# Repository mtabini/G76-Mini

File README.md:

# G76 Mini - A $10 VGA interface for homebrew retrocomputing

The G76 Mini is a simple and inexpensive VGA module for homebrew retrocomputing projects. It requires only a handful of easy-to-procure components and can be either integrated into SBC designs or as a standalone board that can interface with most 8-bit architectures (though it was built with the 6502 in mind). You can view a demo of the interface running [on YouTube](https://youtu.be/on7V5krxY_A).

The hardware design uses the EPM240 from the [Max II family](https://www.intel.com/content/dam/altera-www/global/zh_CN/pdfs/literature/hb/max2/max2_mii5v1_01.pdf) by Altera (now Intel), but the SystemVerilog code should be easily portable to other CPLDs or FPGAs, since it doesn't use any proprietary IP. The EPM240, while technically obsolete, can easily be obtained for around $3 (as of May 2022) on eBay or AliExpress; with the added cost of SRAM and passives, the interface can be incorporated into an existing design for around $5, or built as a standalone board for around $10.

It is additionally possible to completely avoid having to solder SMD parts by purchasing a MAX II EPM240 minimal development board and building a shield on top of it. These typically cost $10 on sites like AliExpress and come with a USB Blaster JTAG programmer to boot.

## Features

The G76 Mini supports these features:

- Completely asynchronous operation; you should be able to just bitbang data into the registers at the typical speeds supported by most hobbyist retrocomputing projects.
- 320x240 resolution at 8BPP (RRRGGGBB), rendered as a 640x480 @ 60Hz standard VGA signal.
- 640x240 resolution at 4BPP “high res” mode using a CGA-like palette, capable of 80x30 text (though you will have to implement the text rendering in software).
- Full read and write access to the video RAM through a set of interface registers.
- Hardware-accelerated vertical scrolling (handy for text displays).
- Toggable self-incrementing X coordinate for faster data transfers.
- Active-low interrupt when entering the non-visible area at the bottom of the screen.

### Features that almost made the cut

The design doesn't support tiling or sprites; there just isn't enough space for them in the EPM240. This is something that I eventually plan to add (possibly after some additional cleanup), but it will likely require more expensive—or, at least, more powerful—hardware.

It should be possible to rewrite the video rendering code to use the 640x400 @ 72Hz VGA mode, thus supporting 8PP even in high-res mode. I am not sure, however, that the design would still fit in an EPM240, and every monitor in my possession struggles to support that resolution, so I didn't really bother with it. An interesting alternative would be to still use 640x480 @ 60Hz, but only render 400 vertical lines through the judicious use of borders.

Finally, there currently is no reset mechanism. Though initially an oversight, this eventually proved to be a requirement to fit the design within the available number of gates.

## Programming guide

The G76 Mini implements 6 addressable 8-bit registers:

| Address | Description |
| --- | --- |
| 0 | Low 8-bits of X coordinate |
| 1 | Bit 0: High bit of X coordinate<br>Bits 1-7: Unused |
| 2 | Y coordinate |
| 3 | Pixel Data |
| 4 | Control<br>Bit 0: Enable/disable X coordinate auto-increment<br>Bit 1: Enable/disable high res mode<br>Bit 2: Enable/disable vertical blank interrupt signal<br>Bit 3: Vertical blank status (read-only)<br>Bits 4-7: Unused<br><br>Writing to this register also clears the vertical blanking interrupt.|
| 5 | Y Offset |

In order to write a single pixel, you first set the X and Y coordinates (in any order), then write the appropriate color value in the Pixel Data register. The new value is placed in the interface's internal memory approximately 60ns later, at which point the system is ready for a new pixel (note, however, that you can start setting new coordinates after only approximately 20ns). Unless auto-increment mode is on, the X and Y coordinates are preserved indefinitely; this helps minimize the need to write data to the coordinate registers, thus speeding up operations.

Reading works in the same way, including support for automatic X-coordinate increment.

### Using auto-increment mode

If Bit 0 of the Control register is set, the internal address pointer is incremented by 1 every time a new value is written to or read from the Pixel Data register. This allows you to read and write entire rows of pixels without having to reset the coordinates every time. 

Note that the increment mechanism is unaware of the system's internal memory layout; thus, if you are in high-res mode, the X coordinate is incremented by _two_ pixels with every access, and, if you exceed the horizontal resolution, you will have to access another 80 values to the Pixel Data register before ending up at the beginning of the next visible line (in practice, you will simply want to reset your coordinates to the beginning of the next line).

### Using hardware-accelerated Y scrolling

Writing a value into the Y Offset register causes the display to be shifted down (that is, scroll up) by a corresponding number of lines. This feature is designed to aid in the implementation of text displays, since the G76 Mini doesn't support any text modes and re-rendering the entire screen would be exceedingly slow. Instead, when the cursor reaches the end of the screen, a new line of text can be rendered beyond the bottom of the display (i.e.: starting at row 240), and then the Y Offset register incremented by the pixel height of the font used.

Note that the Y coordinate register is _relative_ to the Y offset. That means that “Y coordinate 0” is always the top row of the _visible_ portion of the display, regardless of what the Y Offset register is set to.

### Using high-res mode

When bit 1 of the Control register is set, the interface switches to “high res” mode, which displays 640x240 pixels at 4BPP; if you use an 8x8 pixel font, this allows you to display text at 80 columns by 30 rows.

In this mode, each nibble describes a pixel, which is rendered using a palette that approximates the original 16-color CGA mode:

| Value | Color |
| --- | --- |
| 0 | Black |
| 1 | Blue |
| 2 | Green |
| 3 | Cyan | 
| 4 | Red |
| 5 | Magenta |
| 6 | Brown |
| 7 | Grey |
| 8 | Dark grey |
| 9 | Light blue |
| 10 | Light green |
| 11 | Light cyan |
| 12 | Light red |
| 13 | Light magenta |
| 14 | Yellow |
| 15 | White |

Note that the X coordinate register is unaware of the difference in resolution between standard and high-res modes; therefore, you can only really address two pixels at a time, and will always end up accessing an even coordinate by default (e.g.: writing a byte to “x coordinate 0” writes both pixels at `x=0` and `x=1`). This is caused by the fact that, internally, reading a byte value so that individual bits could be updated would be too time-intensive, and so I left it purposefully out of the design. It makes high-res mode much less useful for dynamic display, though it is, of course, still possible to do so.

## Synchronizing with the screen's vertical refresh

If you enable bit 2 of the Control Register, the system brings the  `/VOUT_IRQ` line low when the screen rendering enters the vertical blanking interval, thus allowing you to synchronize your screen updates to the monitor's natural refresh rate for flicker-free animations.

Note that the line remains asserted low until you write any value to the Control register (you can simply read the register and write back onto itself so that you won't make any changes to it), or until you disable interrupts altogether. This is important: If you don't clear the interrupt before exiting your interrupt handler, your computer will likely get stuck in a perpetual loop!

When writing software for a computer that uses the G76 Mini, you should plan for the fact that the interface could be pulling the IRQ line low on soft boot, and therefore should clear it explicitly on boot before you allow the CPU to process interrupts.

If you don't want to deal with interrupts at all, you can simply synchronously observe bit 3 of the Control register, which the interface sets to 1 whenever the raster is in the blanking interval.

## Hardware interface

The hardware interface requires 8 data lines and 3 address lines to access the registers, as well as a Chip Select (active high), and a Read/Write (active low) line. Data is written on the rising edge of Read/Write when Chip Select is high. Data and address lines need to be valid for approximately 20ns after Read/Write rises to allow the CPLD to read the values.

Optionally, a `/VOUT_IRQ` line, active low, can be used to detect when the display raster enters the non-visible zone at the end of the screen; this enables synchronized rendering to avoid flickering.

The interface operates at 3.3V and is **not 5V safe.** Interoperation with a 5V design should be possible using a level shifter, but this is as yet untested.

## Interfacing considerations

The G76 Mini reads data when the `MPU_CS` signal goes high (and, for write operations, when the `/MPU_WE` signal goes low). This makes it compatible with most 8-bit CPUs like the Z80 and 6502, so long as you provide the glue logic required to control the `MPU_CS` signal.

In a design based on the 6502, this means that you will need to qualify `MPU_CS` with the CPU's clock signal, because the CPU doesn't place a valid address on the bus until the high part of the clock cycle. Thus, `MPU_CS` can only go high at the same time as the `PHI2` signal that provides the clock.

## Reference design

I have included a [simple reference design](/reference_design/schematic.pdf) ([B/W version](/reference_design/schematic_bw.pdf)) for a standalone video card in the project. As you can see from the schematic, the interface really only needs a handful of components and is quite simple, since it depends so heavily on the CPLD.

The VGA output is generated using a few resistors, and is of surprisingly good quality, especially if you stick with 1% tolerances. An R2R network might produce a more consistent result, and of course a DAC would be best, but it seemed overkill for a homebrew project.

I picked the [CY7C1018DV33-10VXI](https://www.mouser.ca/datasheet/2/100/CYPR_S_A0001416448_1-2540640.pdf), an inexpensive (about $3.50 from any major North American distributor as of April 2022) 128kiB, 10ns SRAM chip from Cypress as the video memory for the reference design. I suspect that any 3.3V-compatible chip with cycle times of 20ns or faster would work equally well, though I have not tested with anything else.

### Programming the CPLD

The Max II can be programmed using Altera's [USB Blaster](https://www.intel.com/content/www/us/en/products/sku/215633/intel-fpga-download-cable/specifications.html), which has been imaginatively renamed the “FPGA Download Cable” by Intel. (Perhaps they should change their name to “Chip Manufacturing Corporation”.) Clones of the USB Blaster are readily available on Amazon, eBay, and AliExpress for just a few dollars—in fact, most sellers bundle it with their Max II development boards, which are sometimes cheaper than the JTAG programmer alone.

The G76 Mini's SystemVerilog source can be compiled using Quartus II; you should be able to just open the [VGA320.qpf](./VGA320.qpf) project and, provided that you use the same pinout as I did, compile and write it to the hardware. 

Figuring out how to actually connect the CPLD to your computer can be a frustrating experience; the Max II is officially obsolete, and supported only by older versions of Quartus. Unfortunately, these come with unsigned drivers that cannot be installed on Windows 10, leading to much confusion.

In the end, this process worked for me:

- Install [Quartus II Web Edition 13.0sp1](https://www.intel.com/content/www/us/en/software-kit/711791/intel-quartus-ii-web-edition-design-software-version-13-0sp1-for-windows.html), which includes the IP required to compile against the Max II.
- Then install [Quartus II Prime Lite 21.1](https://www.intel.com/content/www/us/en/software-kit/684216/intel-quartus-prime-lite-edition-design-software-version-21-1-for-windows.html), which includes drivers for USB Blaster that are compatible for Windows 10.

You can then use Quartus II Prime Lite 21.1 to both compile and upload your design to the CPLD. Note, however, that I arrived at this setup after much fidgeting with both the software and the operating system, so it's possible that I did something else in addition to installing those two pieces of software and don't remember. As always, YMMV.

### Theory of operation

The system is written in SystemVerilog and is composed of four main modules:

- [VGA](./VGA.sv) is the top-level interface that glues everything together and connects to the outside world.
- [MemoryManager](./memory_manager.sv) provides overall pacing synchronized to the main 50MHz clock signal, and primarily dictated by having to share access to the external RAM between video output and MPU write access.
- [VideoOutput](./video_output.sv) generates the VGA output and sync signals, in addition to the vertical refresh IRQ.
- [MPUInterface](./mcu_interface.sv) manages the interface with the external processing unit bus.

MemoryManager operates on a sequence made up of four clock cycles:

- During the first clock cycle, it reads the byte at the address requested by the VideoOutput module and sets up either a read or write operation if requested by MPUInterface.
- During the second cycle, it starts the read or write operation, if one is pending.
- During the third cycle, it concludes the read or write operation and notifies MPUInterface. If a read was requested, the it also makes the corresponding data available.
- During the last cycle, it sets the memory bus up for the next video data read.

This effectively results in 2 memory operations occurring at 12.5MHz, which is sufficient for a horizontal resolution of 320 pixels at 8BPP. Given that the CY7C1018DV33 has a read/write cycle of 10ns, there is plenty of headroom, and a faster clock (or cleverer algorithm) may result in more bandwidth.

The VideoOutput module is little more than a glorified counter; it simply keeps track of the raster position, issues the appropriate sync signals to the VGA interface, and ensures that the right pixel is being output at all times. Note that the system operates at a pixel clock 25MHz, which is _technically_ out of spec, as [the standard](http://tinyvga.com/vga-timing/640x480@60Hz) expects 25.175MHz. I suspect that most modern monitors will be fine with it (mine reports a 61Hz signal, but doesn't seem to care), but older CRTs may be unhappy and possibly even damaged by the signal. Please keep this in mind!

When it receives a request to write pixel data, MPUInterface raises a flag that is synchronized with the main clock; when the sync occurs, the code sends a write requests to MemoryManager. Thus, while a write should take around 60ns, it should be possible to start writing new data to the coordinate registers much sooner. In my tests, the interface works flawlessly with a 6502 running at 13MHz (which is the fastest clock supported by my experimental computer--the G76 Mini may actually work at even faster speeds).

## Reporting bugs and contributing

This is only my first Verilog project, and my background is not in hardware design. While things seem to work to me, I suspect that there are plenty of bugs, and that the design could be optimized significantly. If you find something broken, please open an issue—and if you would like to contribute any enhancements, please open a PR.

Do note that I am also not a Windows user… if you're having trouble installing Quartus or the USB Blaster drivers, I will probably be of limited use.

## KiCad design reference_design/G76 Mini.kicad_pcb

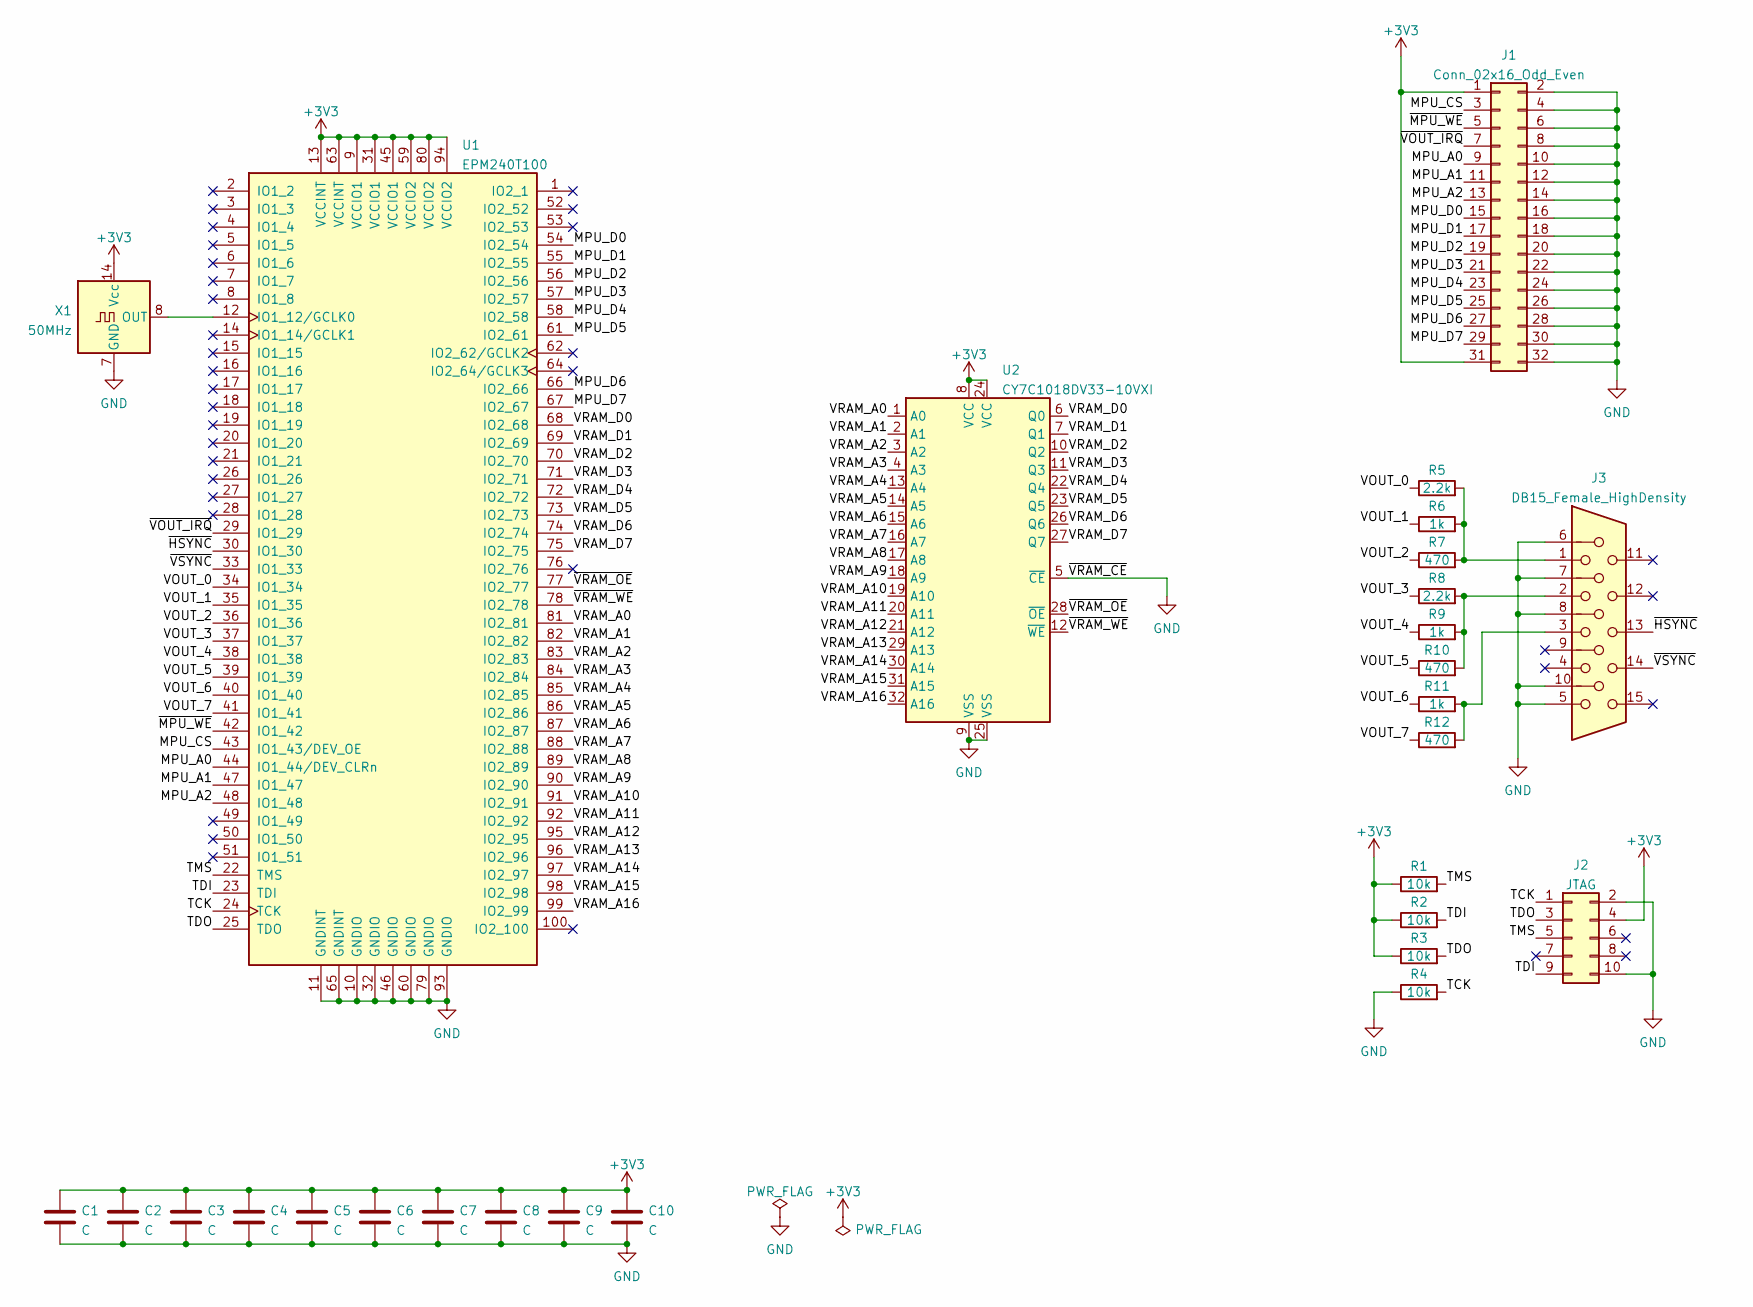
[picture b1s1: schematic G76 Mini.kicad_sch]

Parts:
C1, C2, C3, C4, C5, C6, C7, C8, C9, C10: C; C_1206_3216Metric_Pad1.33x1.80mm_HandSolder
J1: Conn_02x16_Odd_Even; PinHeader_2x16_P2.54mm_Vertical
J2: JTAG; PinHeader_2x05_P2.54mm_Vertical
J3: DB15_Female_HighDensity; DSUB-15-HD_Female_Horizontal_P2.29x1.98mm_EdgePinOffset9.40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
R1, R2, R3, R4: 10k; R_1206_3216Metric_Pad1.30x1.75mm_HandSolder
R5, R8: 2.2k; R_1206_3216Metric_Pad1.30x1.75mm_HandSolder
R6, R9, R11: 1k; R_1206_3216Metric_Pad1.30x1.75mm_HandSolder
R7, R10, R12: 470; R_1206_3216Metric_Pad1.30x1.75mm_HandSolder
U1: EPM240T100; LQFP-100_14x14mm_P0.5mm
U2: CY7C1018DV33-10VXI; JSOP32_7.62mm
X1: 50MHz; Oscillator_DIP-14

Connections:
+3V3: C1.1, C2.1, C3.1, C4.1, C5.1, C6.1, C7.1, C8.1, C9.1, C10.1, J1.1, J1.31, J2.4, R1.1, R2.1, R3.1, U1.9 (VCCIO1), U1.13 (VCCINT), U1.31 (VCCIO1), U1.45 (VCCIO1), U1.59 (VCCIO2), U1.63 (VCCINT), U1.80 (VCCIO2), U1.94 (VCCIO2), U2.8 (VCC), U2.24 (VCC), X1.14 (Vcc)
/MPU_A0: J1.9, U1.44 (IO1_44/DEV_CLRn)
/MPU_A1: J1.11, U1.47 (IO1_47)
/MPU_A2: J1.13, U1.48 (IO1_48)
/MPU_CS: J1.3, U1.43 (IO1_43/DEV_OE)
/MPU_D0: J1.15, U1.54 (IO2_54)
/MPU_D1: J1.17, U1.55 (IO2_55)
/MPU_D2: J1.19, U1.56 (IO2_56)
/MPU_D3: J1.21, U1.57 (IO2_57)
/MPU_D4: J1.23, U1.58 (IO2_58)
/MPU_D5: J1.25, U1.61 (IO2_61)
/MPU_D6: J1.27, U1.66 (IO2_66)
/MPU_D7: J1.29, U1.67 (IO2_67)
/TCK: J2.1, R4.2, U1.24 (TCK)
/TDI: J2.9, R2.2, U1.23 (TDI)
/TDO: J2.3, R3.2, U1.25 (TDO)
/TMS: J2.5, R1.2, U1.22 (TMS)
/VOUT_0: R5.1, U1.34 (IO1_34)
/VOUT_1: R6.1, U1.35 (IO1_35)
/VOUT_2: R7.1, U1.36 (IO1_36)
/VOUT_3: R8.1, U1.37 (IO1_37)
/VOUT_4: R9.1, U1.38 (IO1_38)
/VOUT_5: R10.1, U1.39 (IO1_39)
/VOUT_6: R11.1, U1.40 (IO1_40)
/VOUT_7: R12.1, U1.41 (IO1_41)
/VRAM_A0: U1.81 (IO2_81), U2.1 (A0)
/VRAM_A1: U1.82 (IO2_82), U2.2 (A1)
/VRAM_A2: U1.83 (IO2_83), U2.3 (A2)
/VRAM_A3: U1.84 (IO2_84), U2.4 (A3)
/VRAM_A4: U1.85 (IO2_85), U2.13 (A4)
/VRAM_A5: U1.86 (IO2_86), U2.14 (A5)
/VRAM_A6: U1.87 (IO2_87), U2.15 (A6)
/VRAM_A7: U1.88 (IO2_88), U2.16 (A7)
/VRAM_A8: U1.89 (IO2_89), U2.17 (A8)
/VRAM_A9: U1.90 (IO2_90), U2.18 (A9)
/VRAM_A10: U1.91 (IO2_91), U2.19 (A10)
/VRAM_A11: U1.92 (IO2_92), U2.20 (A11)
/VRAM_A12: U1.95 (IO2_95), U2.21 (A12)
/VRAM_A13: U1.96 (IO2_96), U2.29 (A13)
/VRAM_A14: U1.97 (IO2_97), U2.30 (A14)
/VRAM_A15: U1.98 (IO2_98), U2.31 (A15)
/VRAM_A16: U1.99 (IO2_99), U2.32 (A16)
/VRAM_D0: U1.68 (IO2_68), U2.6 (Q0)
/VRAM_D1: U1.69 (IO2_69), U2.7 (Q1)
/VRAM_D2: U1.70 (IO2_70), U2.10 (Q2)
/VRAM_D3: U1.71 (IO2_71), U2.11 (Q3)
/VRAM_D4: U1.72 (IO2_72), U2.22 (Q4)
/VRAM_D5: U1.73 (IO2_73), U2.23 (Q5)
/VRAM_D6: U1.74 (IO2_74), U2.26 (Q6)
/VRAM_D7: U1.75 (IO2_75), U2.27 (Q7)
/~HSYNC: J3.13, U1.30 (IO1_30)
/~MPU_WE: J1.5, U1.42 (IO1_42)
/~VOUT_IRQ: J1.7, U1.29 (IO1_29)
/~VRAM_OE: U1.77 (IO2_77), U2.28 (~OE)
/~VRAM_WE: U1.78 (IO2_78), U2.12 (~WE)
/~VSYNC: J3.14, U1.33 (IO1_33)
unnamed: J3.1, R5.2, R6.2, R7.2
unnamed: J3.2, R8.2, R9.2, R10.2
unnamed: J3.3, R11.2, R12.2
unnamed: U1.12 (IO1_12/GCLK0), X1.8 (OUT)

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
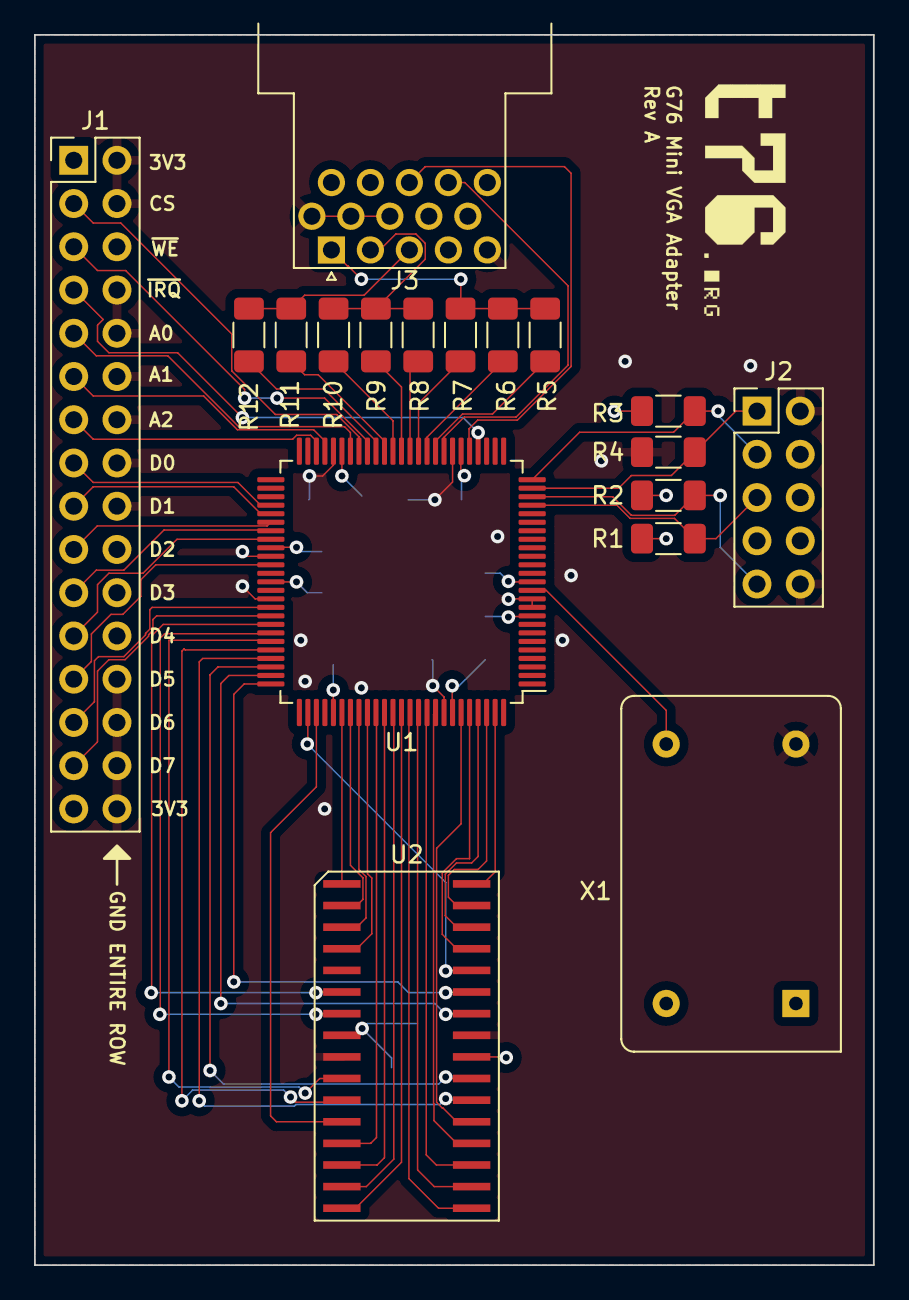
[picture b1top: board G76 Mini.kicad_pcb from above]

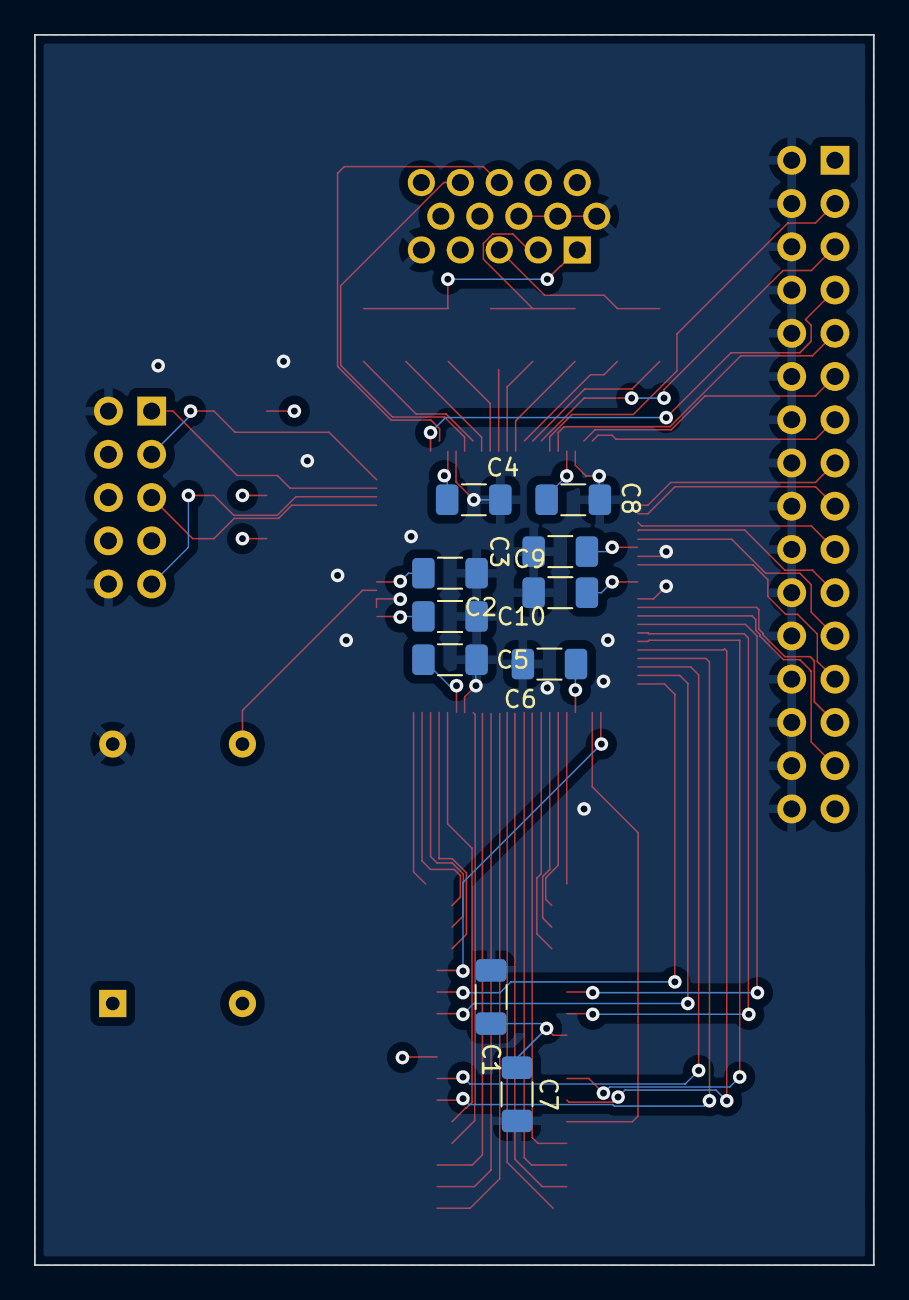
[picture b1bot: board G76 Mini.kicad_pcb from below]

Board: 4 copper layers, 49.3 x 72.3 mm, 28 parts (10 on the bottom side), 61 nets.

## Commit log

2022-03-27 Add asynchronous MCU interface.
2022-03-27 Cleanup
2022-03-27 Pack memory
2022-03-27 Park changes
2022-03-28 Sync working
2022-03-28 Anticipate data bus setup before writes
2022-03-28 Tweak timing of address setup to reduce snow.
2022-03-29 Remove register reads
2022-03-29 Add autobox functionality
2022-04-01 Minor refactor of address
2022-04-01 Clean up autobox
2022-04-01 Clean up state
2022-04-01 Move state into the memory manager
2022-04-01 Move states inside memory manager
2022-04-01 Switch to using addresses instead of coordinates
2022-04-02 Eliminate stray pixels
2022-04-02 Go back to coordinates
2022-04-02 Auto increment working
2022-04-02 Commit to write-only register
2022-04-02 Rename register
2022-04-02 Get rid of my horrible test benches
2022-04-02 Add support for Y offset
2022-04-03 Add support for 640x240
2022-04-03 Remove unused file
2022-04-03 Add license
2022-04-03 Add readme and reference design.
2022-04-03 Fix link
2022-04-03 Add image
2022-04-03 Fix image refs
2022-04-03 Fix readme
2022-04-03 Fix links
2022-04-03 Typo
2022-04-25 Fix pin assignments
2022-04-25 Fix CE line on RAM
2022-05-09 Update schematics and MPU interface
2022-05-15 Implement initial read support
2022-05-21 Add video RAM read support
2022-05-21 Add support for vblank interrupt and bit
2022-05-21 Fix r/w bug
2022-07-07 Improve interrupt handling
